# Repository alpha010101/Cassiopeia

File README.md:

筐体内でLED用の配線を中継するための基板

SchematicとPCB_Layoutの入力にAutodesk-Eagle無償版を使用し、elecrowで製造することを前提にガーバーを作成

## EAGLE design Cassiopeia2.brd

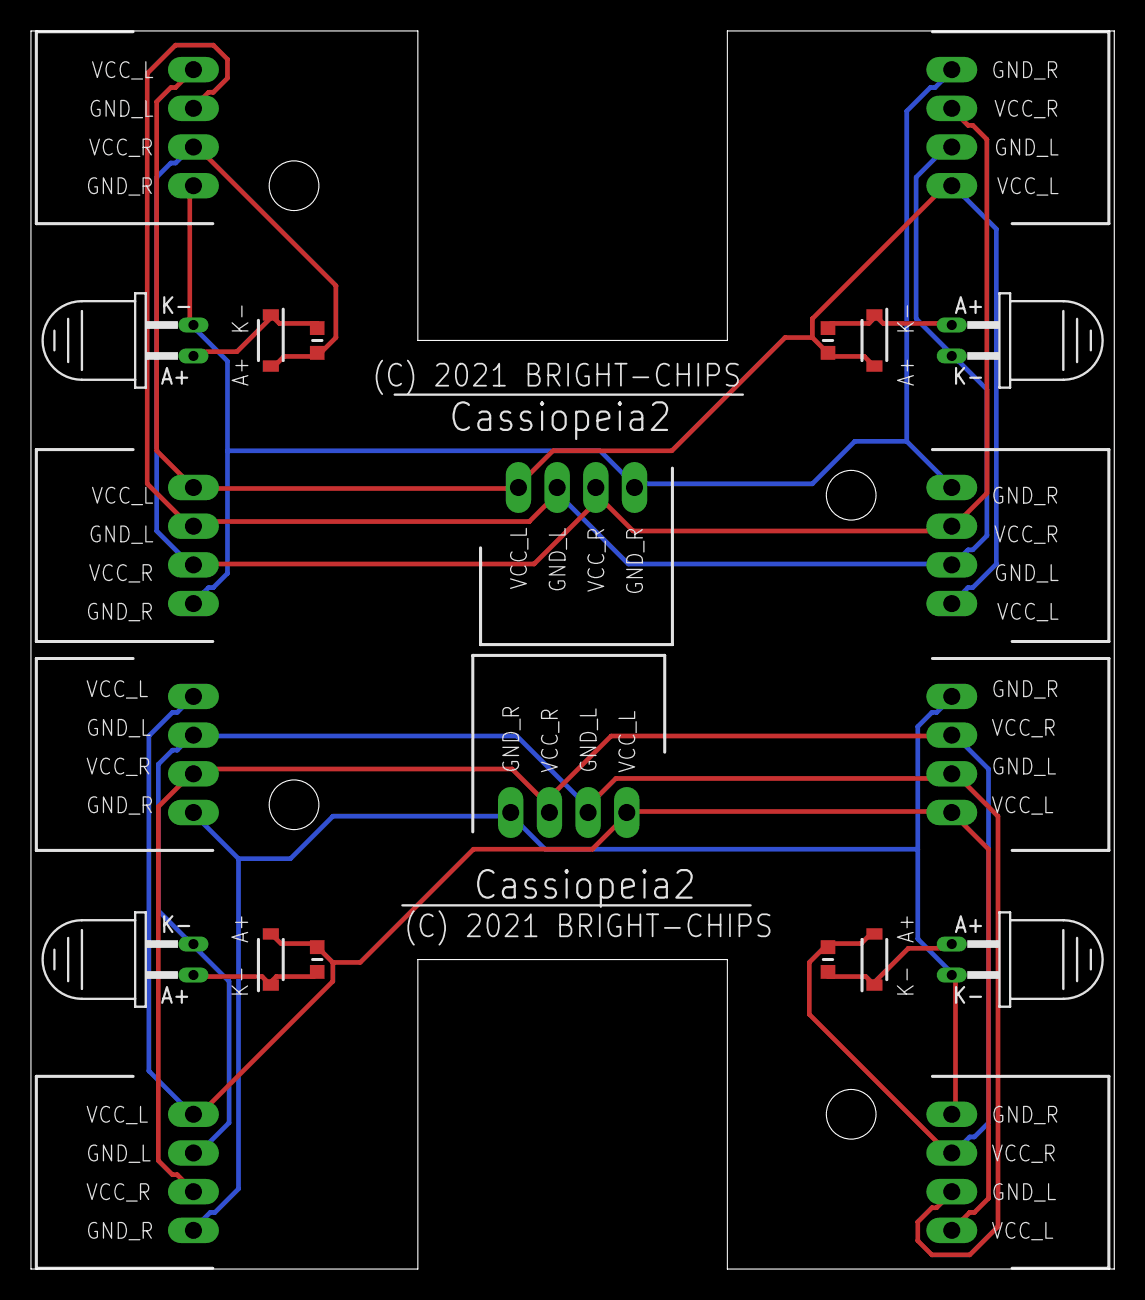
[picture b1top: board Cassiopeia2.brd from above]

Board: 2 copper layers, 70.0 x 80.0 mm, 22 parts (0 on the bottom side), 12 nets.

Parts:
CAPH, CAPH1: SPAD_4PIN; SAPD_4PIN
D1, D2, D3, D4: S-183T; SODFL3516X70N
FULU, FULU1: SPAD_4PIN; SAPD_4PIN
LED_L, LED_L1: LED_FOOT
LED_R, LED_R1: LED_FOOT
R1, R2, R3, R4: RK73B1JTTD103J; RESC1608X55N
RUCHBAH, RUCHBAH1: SPAD_4PIN; SAPD_4PIN
SCHEDAR, SCHEDAR1: SPAD_4PIN; SAPD_4PIN
SEGIN, SEGIN1: SPAD_4PIN; SAPD_4PIN

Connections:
GND_L: CAPH.3, FULU.3, LED_L.K, RUCHBAH.3, SCHEDAR.3, SEGIN.3
GND_L1: CAPH1.3, FULU1.3, LED_L1.K, RUCHBAH1.3, SCHEDAR1.3, SEGIN1.3
GND_R: CAPH.1, FULU.1, LED_R.K, RUCHBAH.1, SCHEDAR.1, SEGIN.1
GND_R1: CAPH1.1, FULU1.1, LED_R1.K, RUCHBAH1.1, SCHEDAR1.1, SEGIN1.1
unnamed: D2.1, LED_R.A, R2.2
unnamed: D1.1, LED_L.A, R1.1
unnamed: D4.1, LED_R1.A, R4.2
unnamed: D3.1, LED_L1.A, R3.1
VCC_L: CAPH.4, D1.2, FULU.4, R1.2, RUCHBAH.4, SCHEDAR.4, SEGIN.4
VCC_L1: CAPH1.4, D3.2, FULU1.4, R3.2, RUCHBAH1.4, SCHEDAR1.4, SEGIN1.4
VCC_R: CAPH.2, D2.2, FULU.2, R2.1, RUCHBAH.2, SCHEDAR.2, SEGIN.2
VCC_R1: CAPH1.2, D4.2, FULU1.2, R4.1, RUCHBAH1.2, SCHEDAR1.2, SEGIN1.2

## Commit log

2025-01-02 initial release

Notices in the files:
Cassiopeia2.brd:
(C) 2021 BRIGHT-CHIPS
